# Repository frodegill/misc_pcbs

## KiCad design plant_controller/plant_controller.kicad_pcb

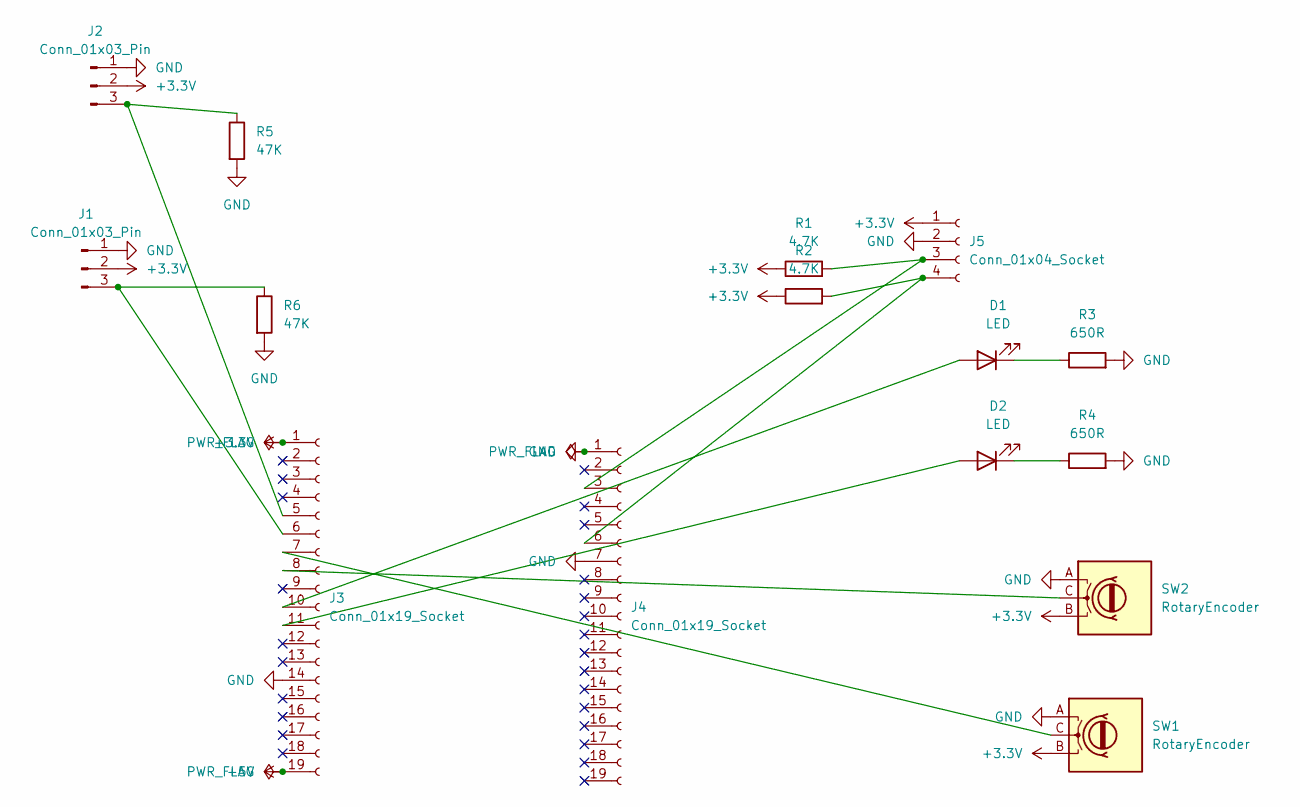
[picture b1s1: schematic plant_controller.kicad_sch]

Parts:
D1, D2: LED; LED_PLCC_2835_AK
J1, J2: Conn_01x03_Pin; TerminalBlock_bornier-3_P5.08mm
J3, J4: Conn_01x19_Socket; PinHeader_1x19_P2.54mm_Vertical
J5: Conn_01x04_Socket; PinHeader_1x04_P2.54mm_Vertical
R1, R2: 4.7K; R_1206_3216Metric
R3, R4: 650R; R_1206_3216Metric
R5, R6: 47K; R_1206_3216Metric
SW1, SW2: RotaryEncoder; RotaryEncoder_Bourns_Vertical_PEC12R-3x17F-Nxxxx

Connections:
+3.3V: J1.2, J2.2, J3.1, J5.1, R1.1, R2.1, SW1.B, SW2.B
+5V: J3.19
GND: J1.1, J2.1, J3.14, J4.1, J4.7, J5.2, R3.2, R4.2, R5.2, R6.2, SW1.A, SW2.A
unnamed: D1.2 (A), J3.10
unnamed: D1.1 (K), R3.1
unnamed: D2.2 (A), J3.11
unnamed: D2.1 (K), R4.1
unnamed: J1.3, J3.6, R6.1
unnamed: J2.3, J3.5, R5.1
unnamed: J3.7, SW1.C
unnamed: J3.8, SW2.C
unnamed: J4.3, J5.3, R1.2
unnamed: J4.6, J5.4, R2.2

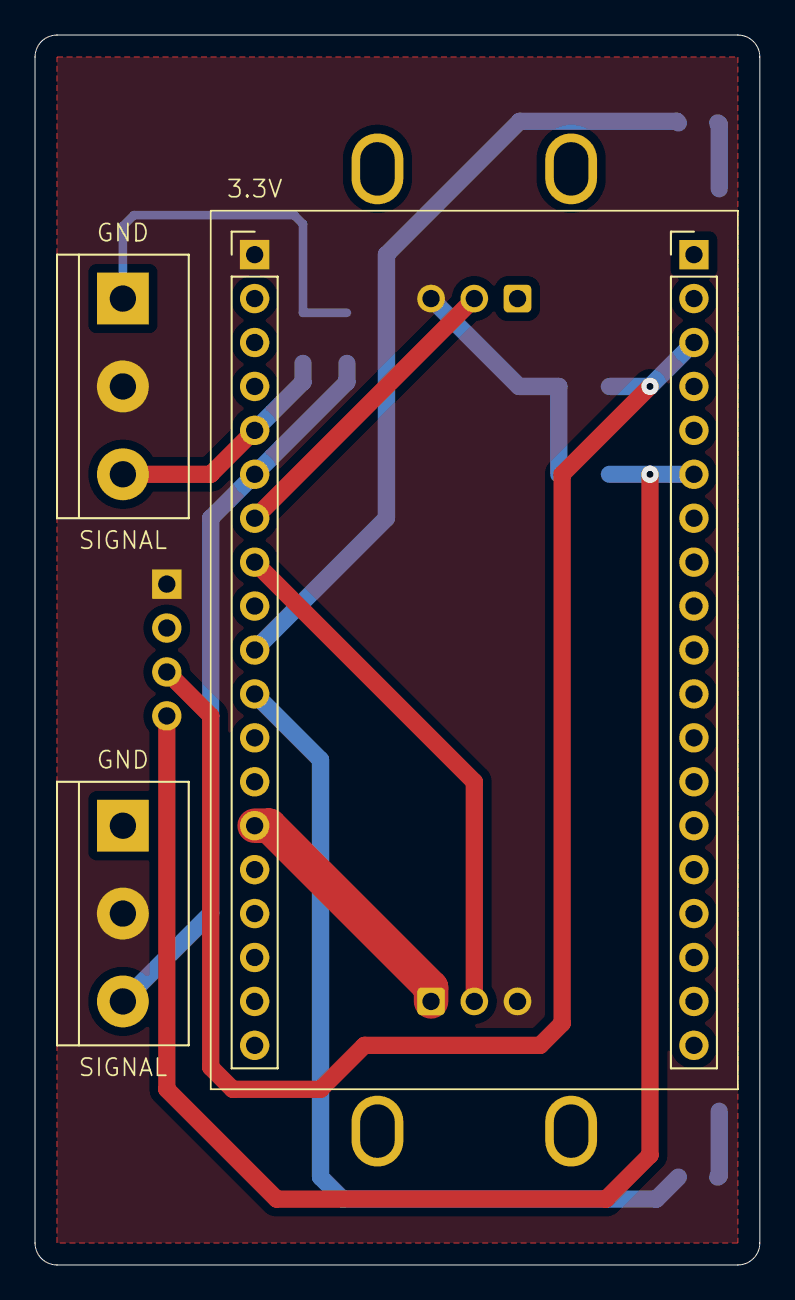
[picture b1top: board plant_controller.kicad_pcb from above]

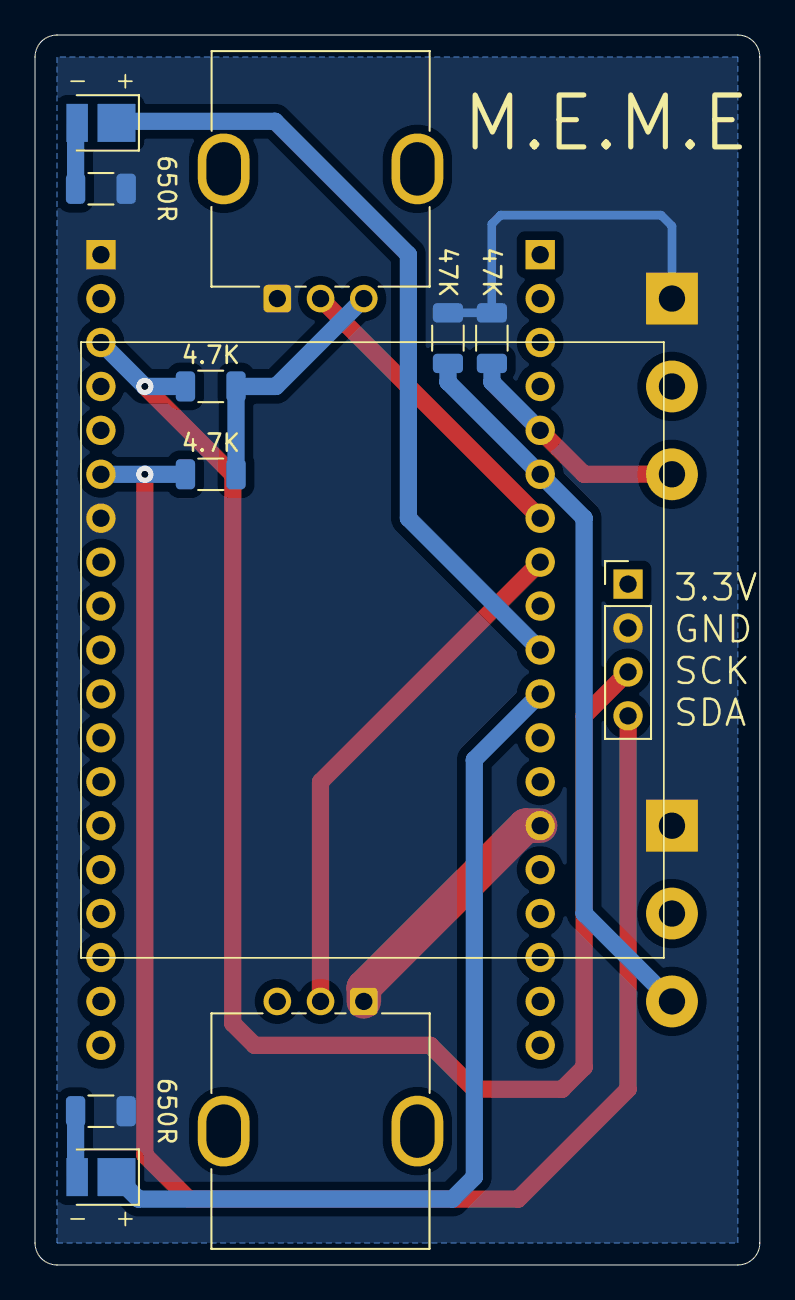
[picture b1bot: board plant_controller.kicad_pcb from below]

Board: 2 copper layers, 41.9 x 71.1 mm, 15 parts (11 on the bottom side), 12 nets.

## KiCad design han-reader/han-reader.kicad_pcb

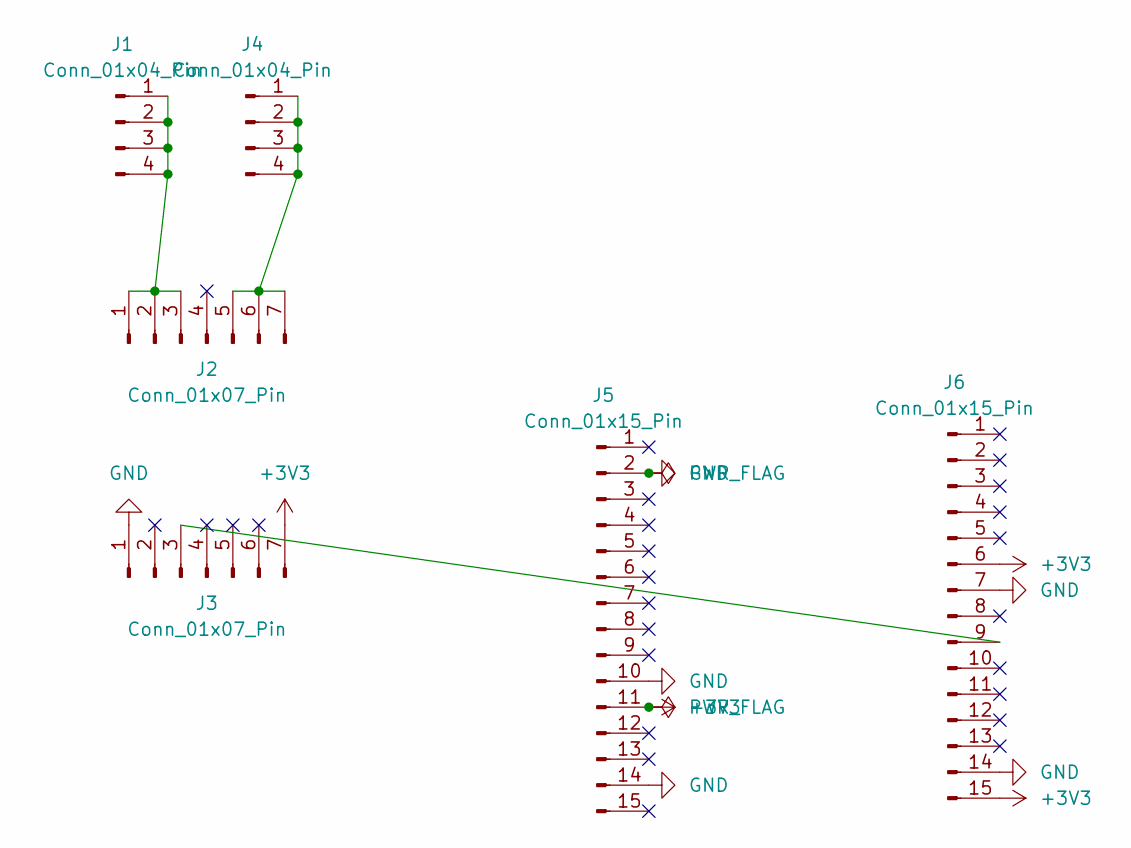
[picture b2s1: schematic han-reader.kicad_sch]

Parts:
J1, J4: Conn_01x04_Pin; PinHeader_1x04_P2.54mm_Vertical
J2, J3: Conn_01x07_Pin; PinHeader_1x07_P2.54mm_Vertical
J5, J6: Conn_01x15_Pin; PinHeader_1x15_P2.54mm_Vertical

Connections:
+3V3: J3.7, J5.11, J6.6, J6.15
GND: J3.1, J5.2, J5.10, J5.14, J6.7, J6.14
unnamed: J1.1, J1.2, J1.3, J1.4, J2.1, J2.2, J2.3
unnamed: J2.5, J2.6, J2.7, J4.1, J4.2, J4.3, J4.4
unnamed: J3.3, J6.9

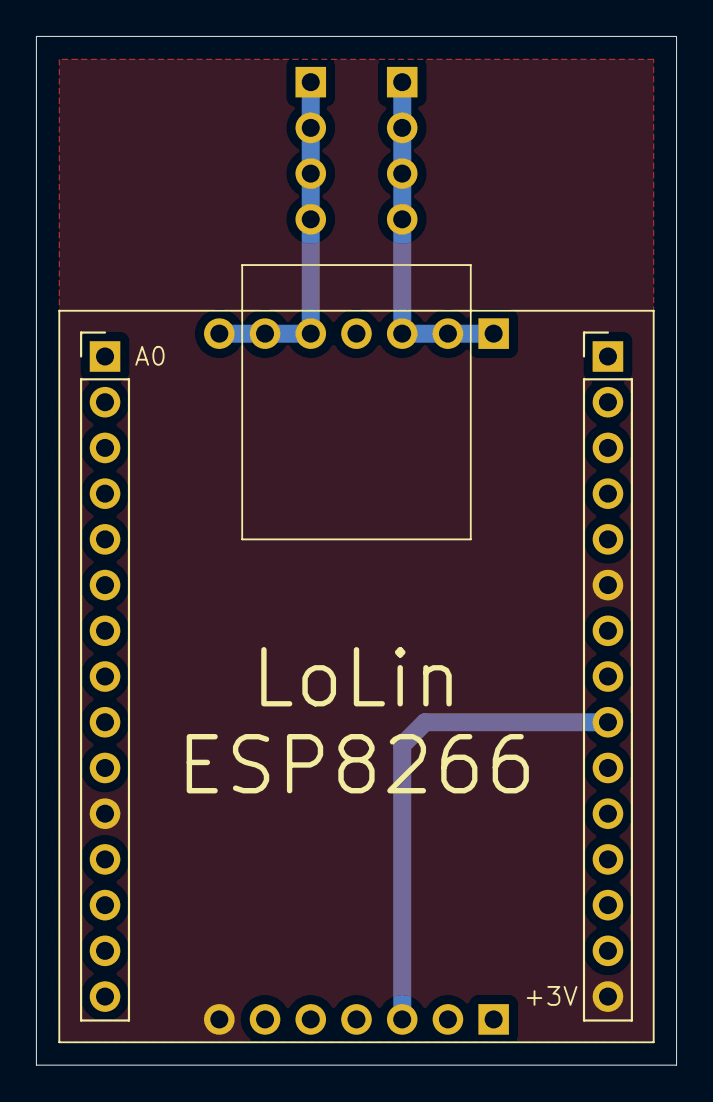
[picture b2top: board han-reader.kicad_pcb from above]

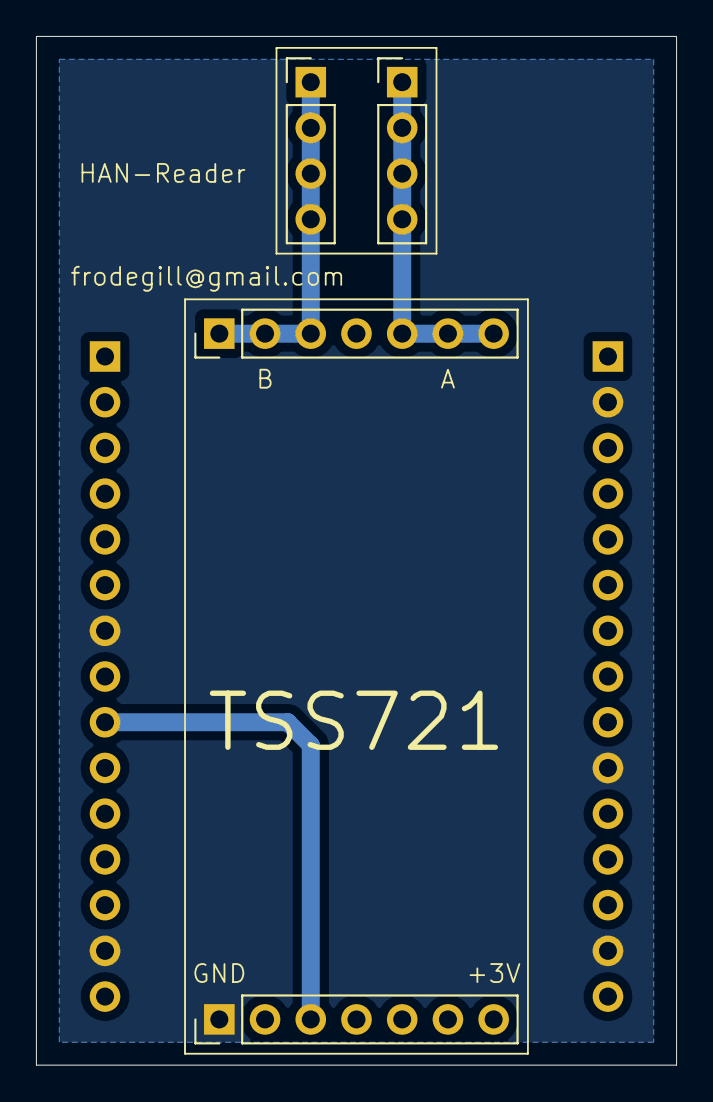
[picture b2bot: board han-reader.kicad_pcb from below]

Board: 2 copper layers, 35.6 x 57.1 mm, 6 parts (4 on the bottom side), 5 nets.

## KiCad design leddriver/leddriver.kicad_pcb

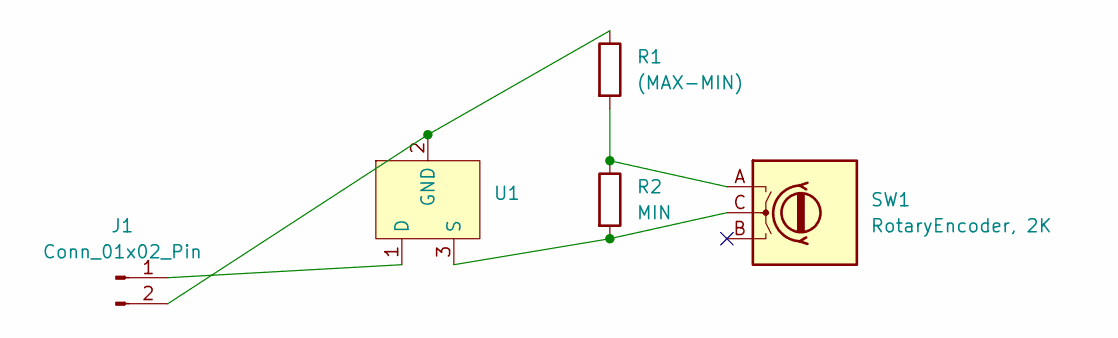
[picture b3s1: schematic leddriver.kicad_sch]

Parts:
J1: Conn_01x02_Pin; PinHeader_1x02_P2.54mm_Vertical
R1: (MAX-MIN); R_1206_3216Metric
R2: MIN; R_1206_3216Metric
SW1: RotaryEncoder, 2K; RotaryEncoder_Bourns_Vertical_PEC12R-3x17F-Nxxxx
U1: SOT-89-3

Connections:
unnamed: J1.1, U1.1 (D)
unnamed: J1.2, R1.1, U1.2 (GND)
unnamed: R1.2, R2.1, SW1.A
unnamed: R2.2, SW1.C, U1.3 (S)

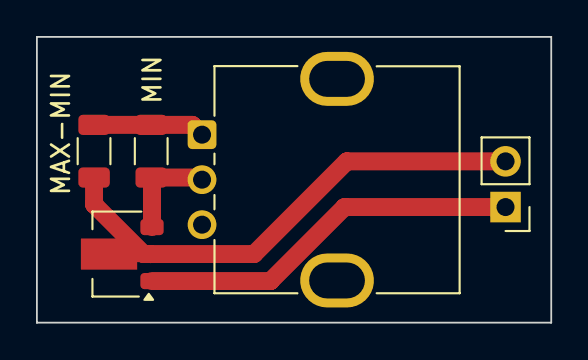
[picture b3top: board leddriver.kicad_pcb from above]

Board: 2 copper layers, 28.6 x 15.9 mm, 5 parts (0 on the bottom side), 4 nets.

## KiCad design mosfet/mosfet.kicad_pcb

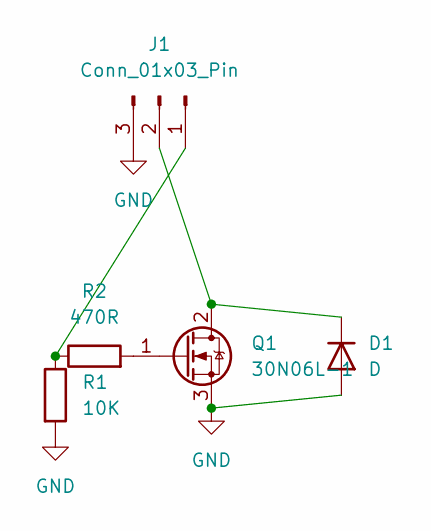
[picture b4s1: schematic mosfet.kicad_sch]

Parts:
D1: D; D_SMB
J1: Conn_01x03_Pin; PinHeader_1x03_P2.54mm_Vertical
Q1: 30N06L-1; TO-252-2
R1: 10K; R_1206_3216Metric
R2: 470R; R_1206_3216Metric

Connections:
GND: D1.2 (A), J1.3, Q1.3 (S), R1.2
unnamed: D1.1 (K), J1.2, Q1.2 (D)
unnamed: J1.1, R1.1, R2.1
unnamed: Q1.1 (G), R2.2

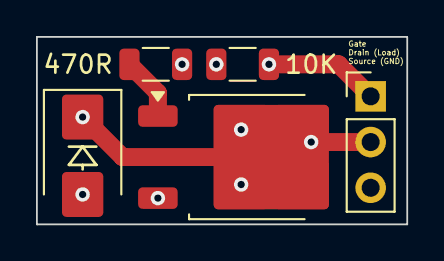
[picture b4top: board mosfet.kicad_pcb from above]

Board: 4 copper layers, 20.6 x 10.4 mm, 5 parts (0 on the bottom side), 4 nets.

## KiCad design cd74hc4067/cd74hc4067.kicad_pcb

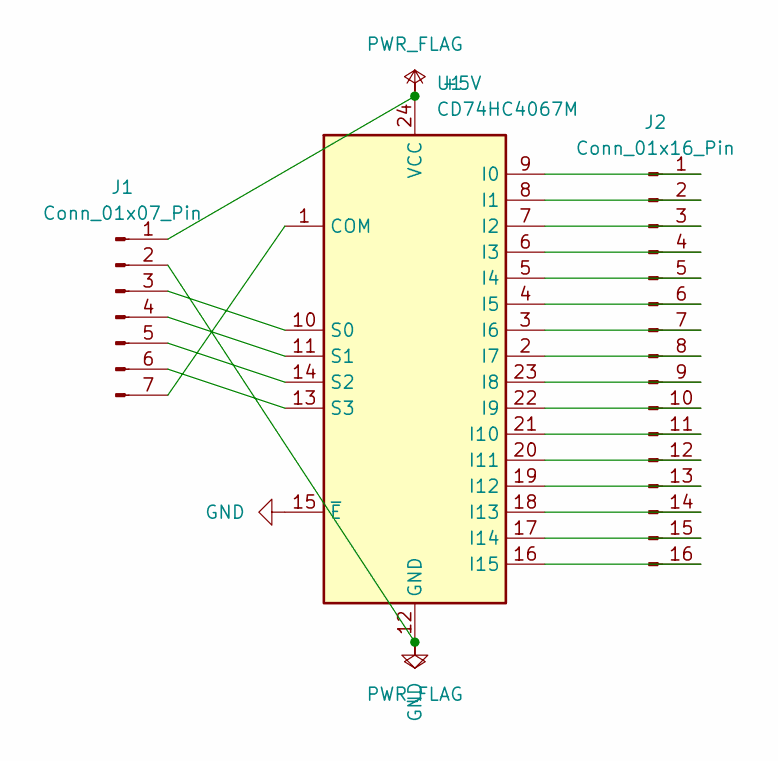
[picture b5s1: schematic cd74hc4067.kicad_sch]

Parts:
J1: Conn_01x07_Pin; PinHeader_1x07_P2.54mm_Vertical
J2: Conn_01x16_Pin; PinHeader_1x16_P2.54mm_Vertical
U1: CD74HC4067M; SOIC-24W_7.5x15.4mm_P1.27mm

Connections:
+5V: J1.1, U1.24 (VCC)
GND: J1.2, U1.12 (GND), U1.15 (~E)
unnamed: J1.3, U1.10 (S0)
unnamed: J1.4, U1.11 (S1)
unnamed: J1.5, U1.14 (S2)
unnamed: J1.6, U1.13 (S3)
unnamed: J1.7, U1.1 (COM)
unnamed: J2.1, U1.9 (I0)
unnamed: J2.2, U1.8 (I1)
unnamed: J2.3, U1.7 (I2)
unnamed: J2.4, U1.6 (I3)
unnamed: J2.5, U1.5 (I4)
unnamed: J2.6, U1.4 (I5)
unnamed: J2.7, U1.3 (I6)
unnamed: J2.8, U1.2 (I7)
unnamed: J2.9, U1.23 (I8)
unnamed: J2.10, U1.22 (I9)
unnamed: J2.11, U1.21 (I10)
unnamed: J2.12, U1.20 (I11)
unnamed: J2.13, U1.19 (I12)
unnamed: J2.14, U1.18 (I13)
unnamed: J2.15, U1.17 (I14)
unnamed: J2.16, U1.16 (I15)

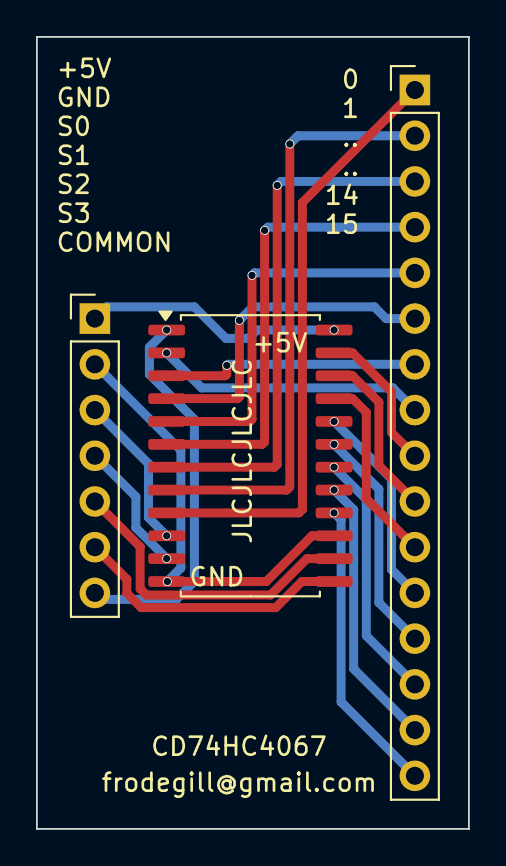
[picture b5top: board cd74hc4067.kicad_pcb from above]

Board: 2 copper layers, 24.0 x 44.0 mm, 3 parts (0 on the bottom side), 23 nets.

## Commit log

2025-01-19 Added CD74HC4067 breakout board
2025-01-19 Added mosfet breakout board
2025-01-19 Aded leddriver breakout board
2025-01-19 Added led breakout board
2025-01-21 Added simple board for connecting HAN-Reader components
2025-01-21 Renamed gerber files
2025-03-18 Added PCB for two analog moisture sensors and OLED screen
2026-02-25 added small plant controller project
